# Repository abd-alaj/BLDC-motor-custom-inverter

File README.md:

Hello, 

this is the start of our casptone project. 

You will see the following structure (with changes if i have forgotten to update this section):  

```
.
├── data/                    - parameters, csv files, oscilloscope data
├── docs/                    - documentation of our project
├── hardware/                - KiCad Project files, scheamtic, footprints, etc.
│   ├── schematics/             - schematic files
│   ├── layout/                 - PCB layout files
│   ├── libraries/              - custom footprints/symbols
│   └── manufacturing/          - gerbers, BOM, etc.
├── models/                 - main simulink directory
│   └── components/              - smaller components for the model
├── scripts/                 - utility matlab scripts
├── src/                     - C code
└── work/                    - MATLAB throws autogenerated files in here 
```

# How To Use This Code
1. git clone this repo: 
```
git clone https://github.com/abd-alaj/BLDC-motor-custom-inverter.git
```
2. open the `BLDC_motor_custom_inverter.m.prj` file in matlab prior to starting any work.

That's it. This project is in a rather primitive state so this readme file is an active WIP.

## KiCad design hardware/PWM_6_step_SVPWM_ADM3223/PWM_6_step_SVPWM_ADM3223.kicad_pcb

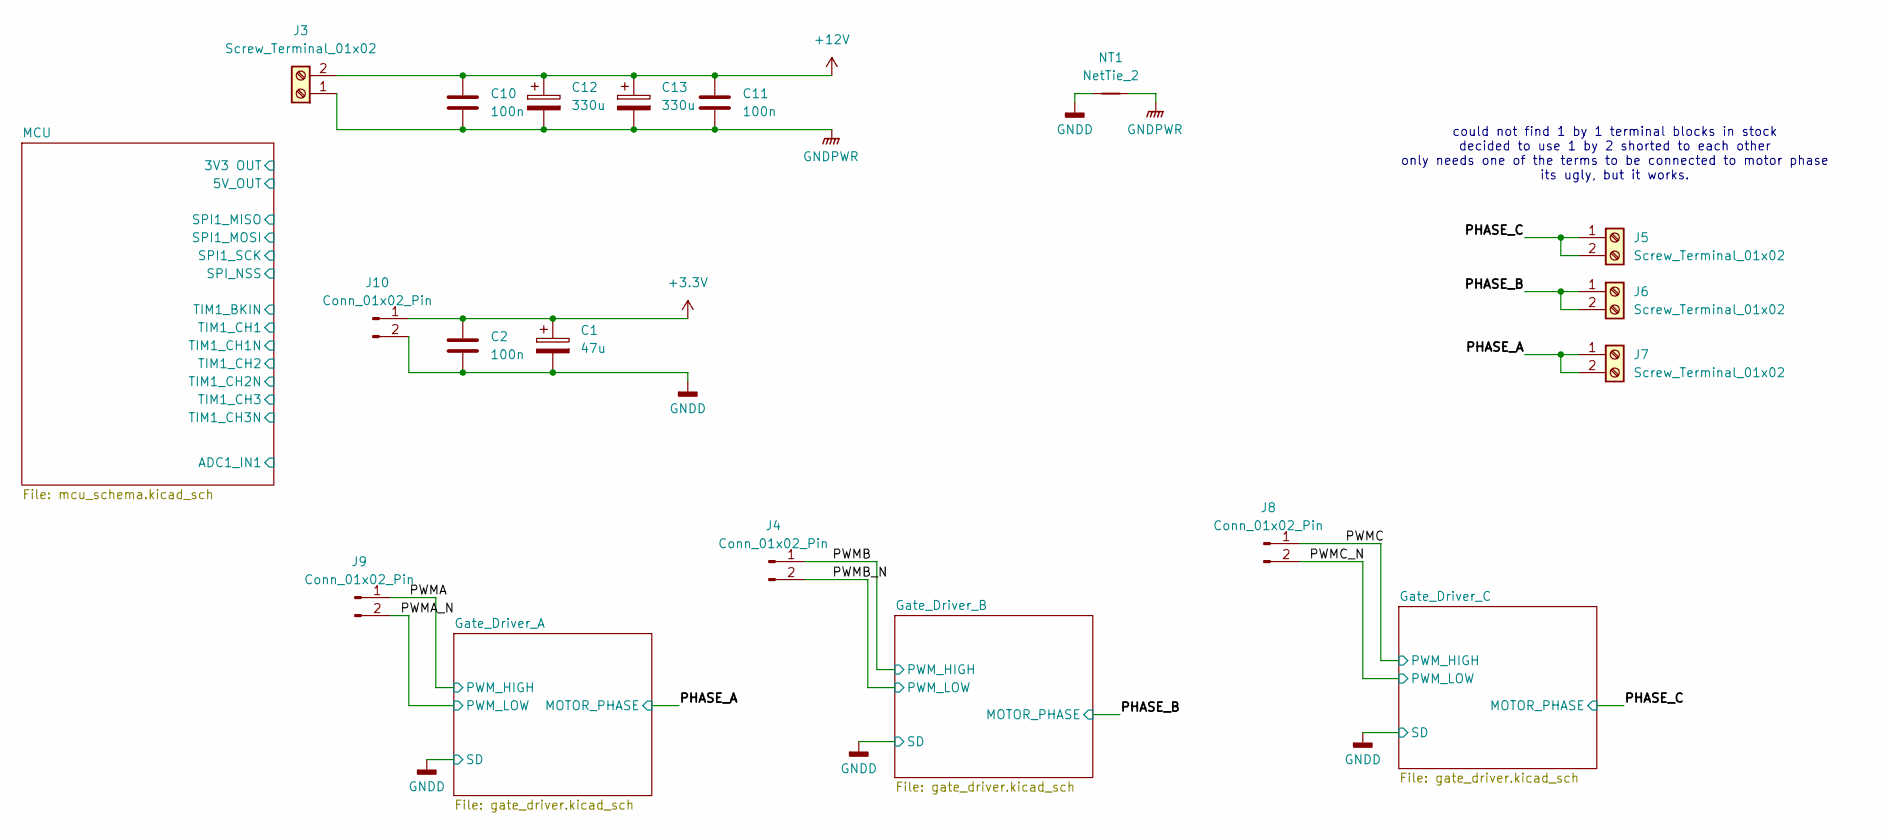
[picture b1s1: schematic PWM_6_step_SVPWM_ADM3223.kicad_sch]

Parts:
C1: 47u; CP_Radial_D8.0mm_P3.50mm
C2, C10, C11: 100n; C_1206_3216Metric
C12, C13: 330u; PCAP_12_5x20-THRU-ELECT_NCA
J3, J5, J6, J7: Screw_Terminal_01x02; TerminalBlock_TE_282834-2_1x02_P2.54mm_Horizontal
J4, J8, J9, J10: Conn_01x02_Pin; PinHeader_1x02_P2.54mm_Vertical
NT1: NetTie_2; NetTie-2_SMD_Pad2.0mm

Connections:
+3.3V: C1.1, C2.1, J10.1; also elsewhere on the board
+12V: C10.1, C11.1, C12.1, C13.1, J3.2; also elsewhere on the board
/PHASE_A: J7.1, J7.2; also elsewhere on the board
/PHASE_B: J6.1, J6.2; also elsewhere on the board
/PHASE_C: J5.1, J5.2; also elsewhere on the board
/PWMA: J9.1; also elsewhere on the board
/PWMA_N: J9.2; also elsewhere on the board
/PWMB: J4.1; also elsewhere on the board
/PWMB_N: J4.2; also elsewhere on the board
/PWMC: J8.1; also elsewhere on the board
/PWMC_N: J8.2; also elsewhere on the board
GNDD: C1.2, C2.2, J10.2, NT1.1; also elsewhere on the board
GNDPWR: C10.2, C11.2, C12.2, C13.2, J3.1, NT1.2; also elsewhere on the board

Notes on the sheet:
could not find 1 by 1 terminal blocks in stock decided to use 1 by 2 shorted to each other only needs one of the terms to be connected to motor phase its ugly, but it works.

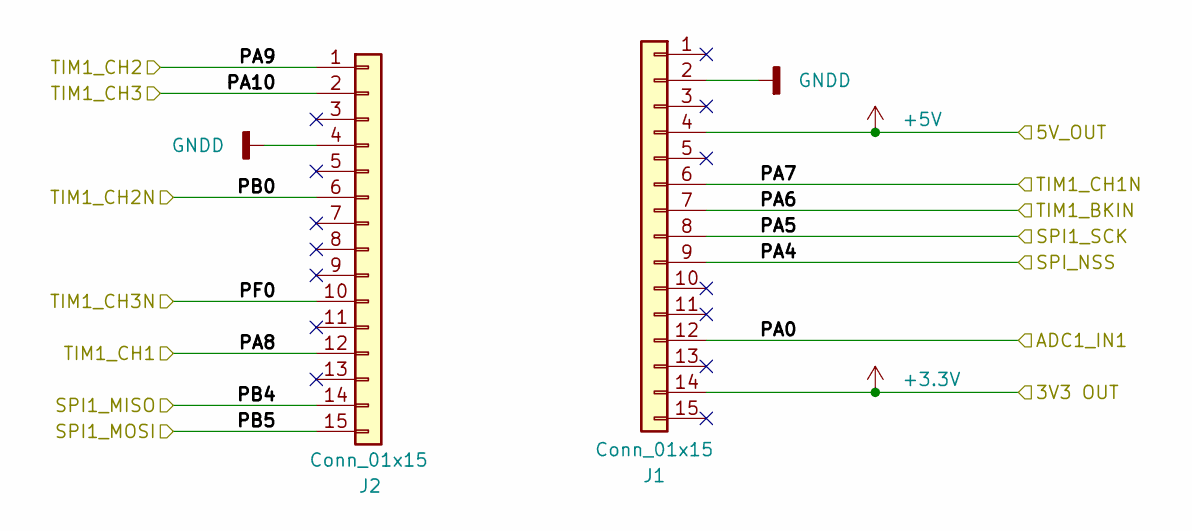
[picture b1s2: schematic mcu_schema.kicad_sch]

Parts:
J1, J2: Conn_01x15; PinSocket_1x15_P2.54mm_Vertical

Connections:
unnamed: J1.2, J2.4

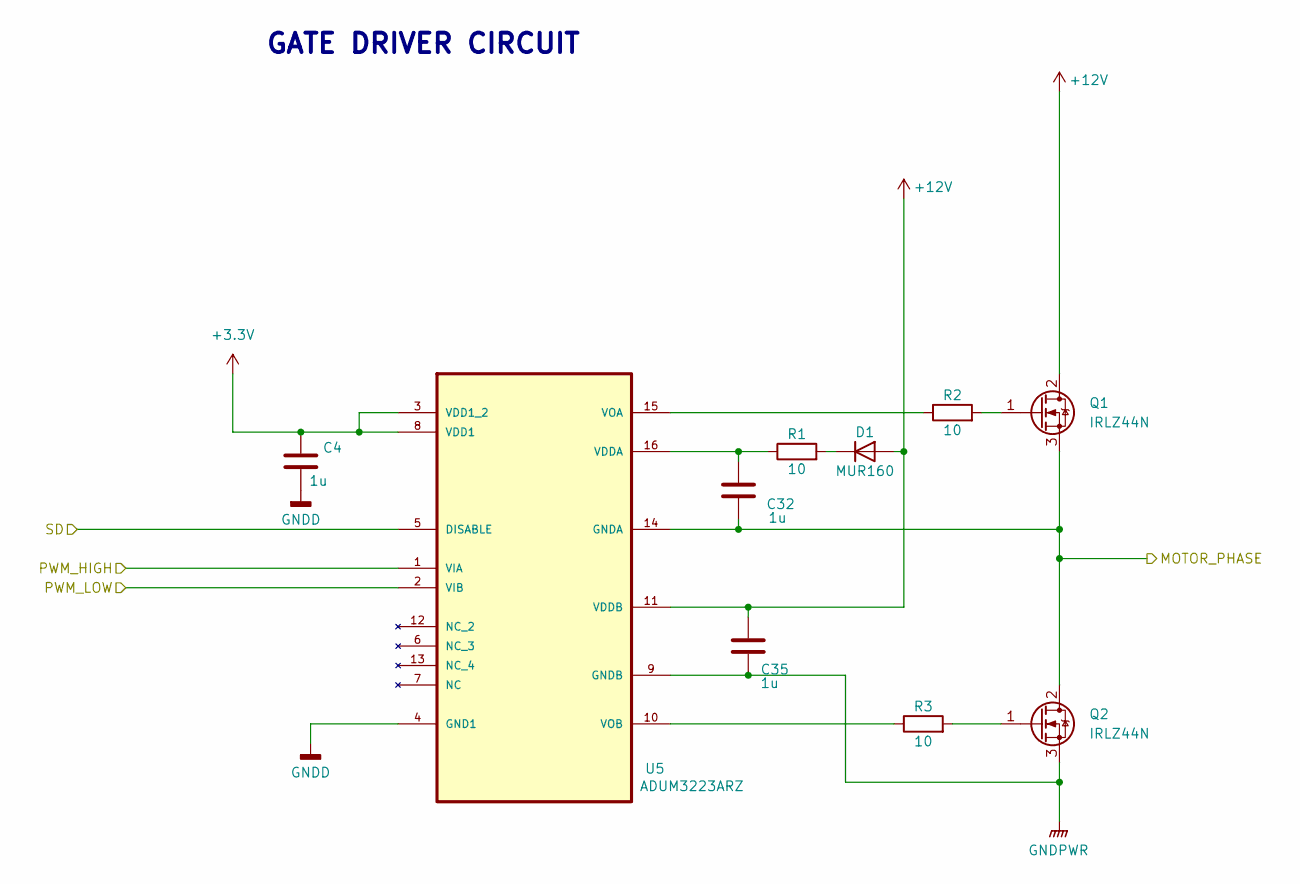
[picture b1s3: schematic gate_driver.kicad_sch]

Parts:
C4, C32, C35: 1u; C_0603_1608Metric
D1: MUR160; D_DO-41_SOD81_P7.62mm_Horizontal
Q1, Q2: IRLZ44N; TO-220-3_Vertical
R1, R2, R3: 10; R_1206_3216Metric
U5: ADUM3223ARZ; SOIC127P600X175-16N; MPN ADUM3223ARZ

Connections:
+3.3V: C4.1, U5.3 (VDD1_2), U5.8 (VDD1); also elsewhere on the board
+12V: C35.1, D1.2 (A), Q1.2 (D), U5.11 (VDDB); also elsewhere on the board
/PHASE_A: C32.2, Q1.3 (S), Q2.2 (D), U5.14 (GNDA); also elsewhere on the board
/PWMA: U5.1 (VIA); also elsewhere on the board
/PWMA_N: U5.2 (VIB); also elsewhere on the board
GNDD: C4.2, U5.4 (GND1), U5.5 (DISABLE); also elsewhere on the board
GNDPWR: C35.2, Q2.3 (S), U5.9 (GNDB); also elsewhere on the board
unnamed: D1.1 (K), R1.2
unnamed: Q1.1 (G), R2.2
unnamed: Q2.1 (G), R3.2
unnamed: C32.1, R1.1, U5.16 (VDDA)
unnamed: R2.1, U5.15 (VOA)
unnamed: R3.1, U5.10 (VOB)

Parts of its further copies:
C5, C9, C33, C34, C36, C37: 1u; C_0603_1608Metric
D2, D3: MUR160; D_DO-41_SOD81_P7.62mm_Horizontal
Q3, Q4, Q5, Q6: IRLZ44N; TO-220-3_Vertical
R4, R5, R6, R7, R8, R9: 10; R_1206_3216Metric
U6, U7: ADUM3223ARZ; SOIC127P600X175-16N; MPN ADUM3223ARZ

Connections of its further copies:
+3.3V: C5.1, C9.1, U6.3 (VDD1_2), U6.8 (VDD1), U7.3 (VDD1_2), U7.8 (VDD1); also elsewhere on the board
+12V: C36.1, C37.1, D2.2 (A), D3.2 (A), Q3.2 (D), Q5.2 (D), U6.11 (VDDB), U7.11 (VDDB); also elsewhere on the board
/PHASE_B: C33.2, Q3.3 (S), Q4.2 (D), U6.14 (GNDA); also elsewhere on the board
/PHASE_C: C34.2, Q5.3 (S), Q6.2 (D), U7.14 (GNDA); also elsewhere on the board
/PWMB: U6.1 (VIA); also elsewhere on the board
/PWMB_N: U6.2 (VIB); also elsewhere on the board
/PWMC: U7.1 (VIA); also elsewhere on the board
/PWMC_N: U7.2 (VIB); also elsewhere on the board
GNDD: C5.2, C9.2, U6.4 (GND1), U6.5 (DISABLE), U7.4 (GND1), U7.5 (DISABLE); also elsewhere on the board
GNDPWR: C36.2, C37.2, Q4.3 (S), Q6.3 (S), U6.9 (GNDB), U7.9 (GNDB); also elsewhere on the board
unnamed: D2.1 (K), R4.2
unnamed: D3.1 (K), R7.2
unnamed: Q3.1 (G), R6.2
unnamed: Q4.1 (G), R5.2
unnamed: Q5.1 (G), R9.2
unnamed: Q6.1 (G), R8.2
unnamed: C33.1, R4.1, U6.16 (VDDA)
unnamed: R6.1, U6.15 (VOA)
unnamed: R5.1, U6.10 (VOB)
unnamed: C34.1, R7.1, U7.16 (VDDA)
unnamed: R9.1, U7.15 (VOA)
unnamed: R8.1, U7.10 (VOB)

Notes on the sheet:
GATE DRIVER CIRCUIT

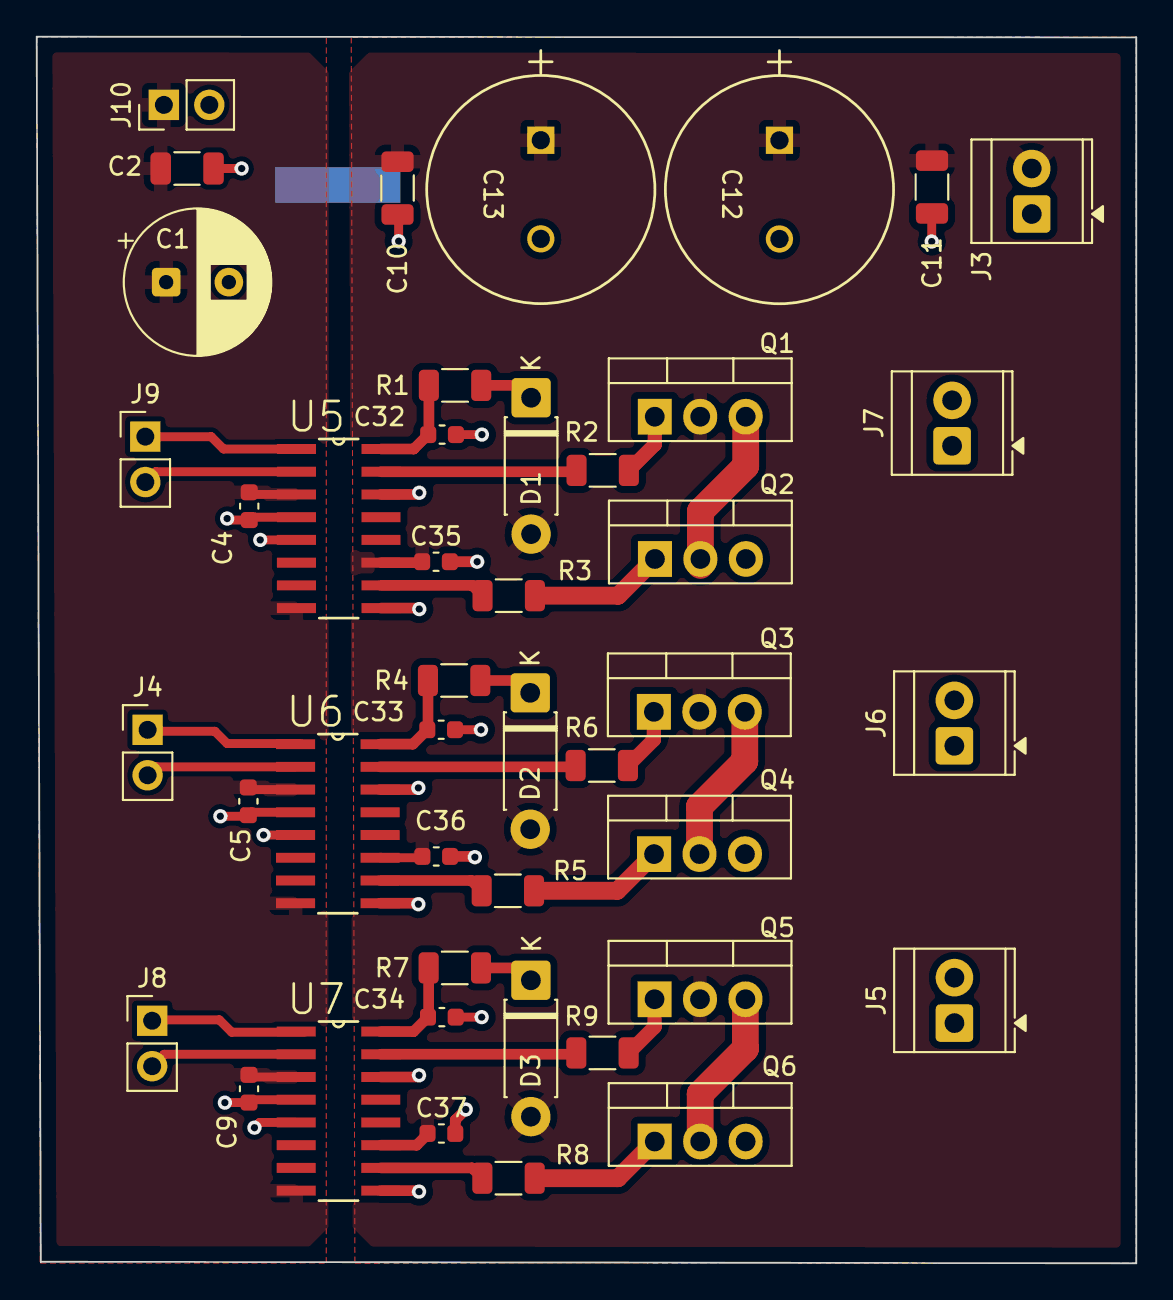
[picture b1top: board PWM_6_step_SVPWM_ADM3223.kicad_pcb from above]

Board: 2 copper layers, 61.4 x 68.5 mm, 45 parts (1 on the bottom side), 31 nets.

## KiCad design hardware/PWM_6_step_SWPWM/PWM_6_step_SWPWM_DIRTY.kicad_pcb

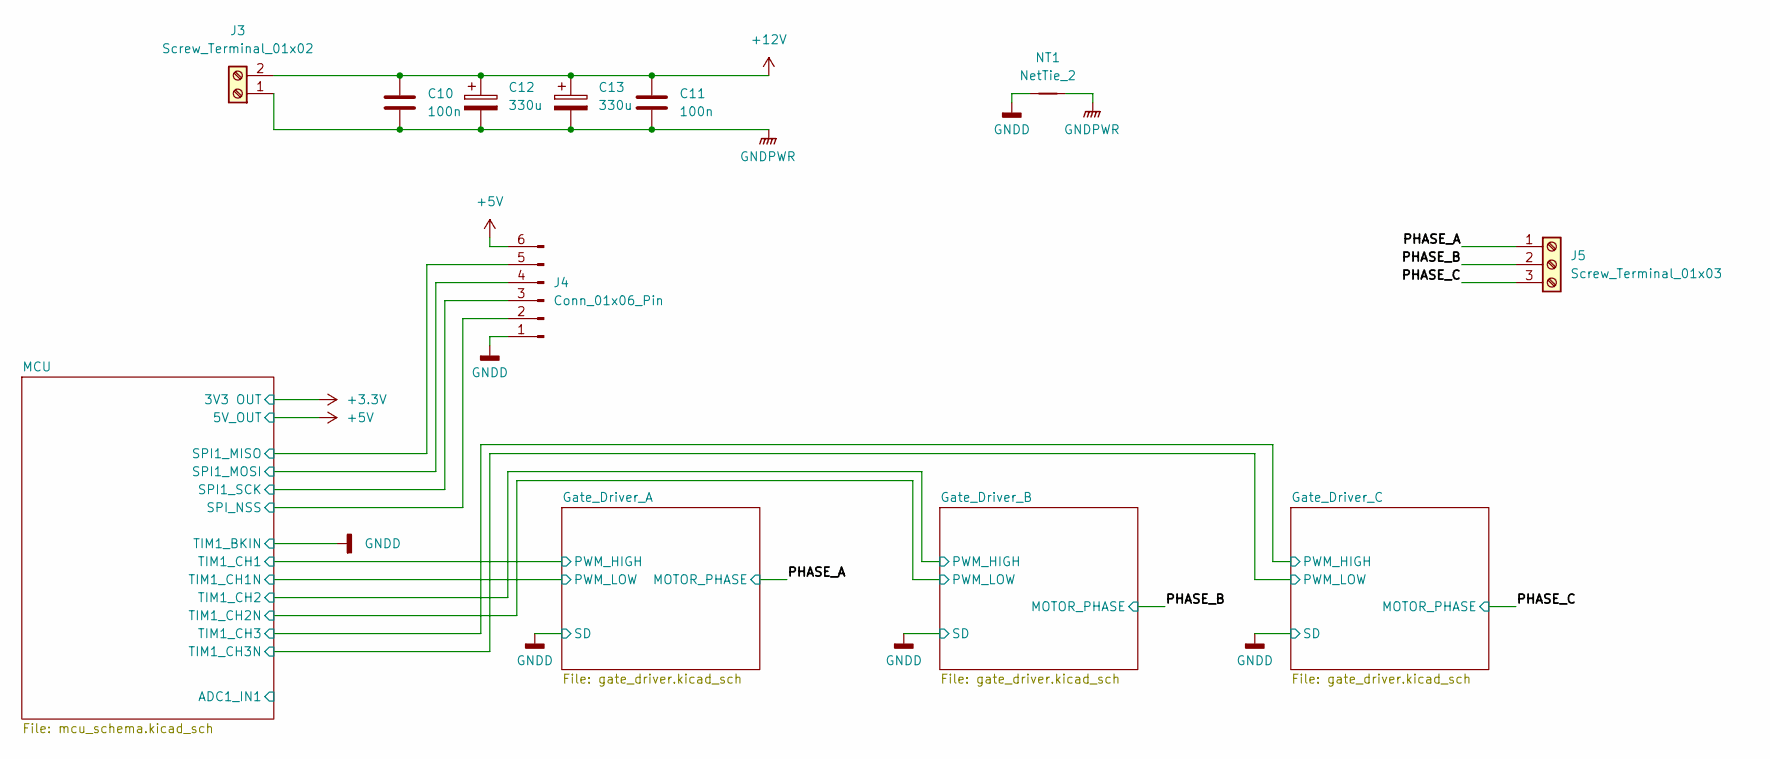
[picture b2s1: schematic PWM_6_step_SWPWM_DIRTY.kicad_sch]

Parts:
C10, C11: 100n; C_1206_3216Metric
C12, C13: 330u; PCAP_12_5x20-THRU-ELECT_NCA
J3: Screw_Terminal_01x02; TerminalBlock_TE_282834-2_1x02_P2.54mm_Horizontal
J4: Conn_01x06_Pin; PinHeader_1x06_P2.54mm_Vertical
J5: Screw_Terminal_01x03; TerminalBlock_TE_282834-3_1x03_P2.54mm_Horizontal
NT1: NetTie_2; NetTie-2_SMD_Pad2.0mm

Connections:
+5V: J4.6; also elsewhere on the board
+12V: C10.1, C11.1, C12.1, C13.1, J3.2; also elsewhere on the board
/MCU/PA4: J4.2; also elsewhere on the board
/MCU/PA5: J4.3; also elsewhere on the board
/MCU/PB4: J4.5; also elsewhere on the board
/MCU/PB5: J4.4; also elsewhere on the board
/PHASE_A: J5.1; also elsewhere on the board
/PHASE_B: J5.2; also elsewhere on the board
/PHASE_C: J5.3; also elsewhere on the board
GNDD: J4.1, NT1.1; also elsewhere on the board
GNDPWR: C10.2, C11.2, C12.2, C13.2, J3.1, NT1.2; also elsewhere on the board

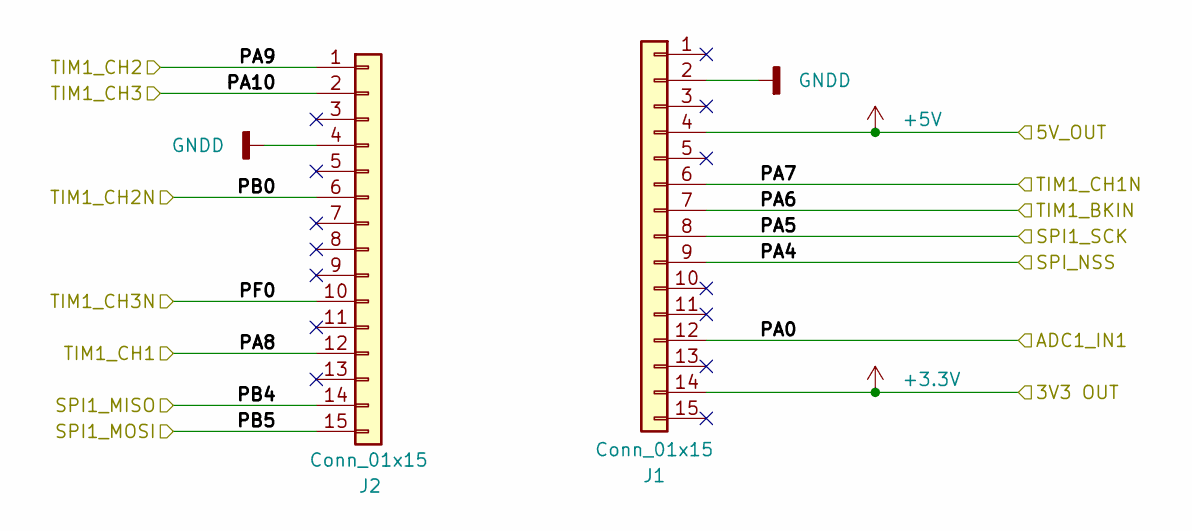
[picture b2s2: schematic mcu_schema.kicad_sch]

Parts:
J1, J2: Conn_01x15; PinSocket_1x15_P2.54mm_Vertical

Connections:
+3.3V: J1.14; also elsewhere on the board
+5V: J1.4; also elsewhere on the board
/MCU/PA0: J1.12
/MCU/PA4: J1.9; also elsewhere on the board
/MCU/PA5: J1.8; also elsewhere on the board
/MCU/PA7: J1.6; also elsewhere on the board
/MCU/PA8: J2.12; also elsewhere on the board
/MCU/PA9: J2.1; also elsewhere on the board
/MCU/PA10: J2.2; also elsewhere on the board
/MCU/PB0: J2.6; also elsewhere on the board
/MCU/PB4: J2.14; also elsewhere on the board
/MCU/PB5: J2.15; also elsewhere on the board
/MCU/PF0: J2.10; also elsewhere on the board
GNDD: J1.2, J1.7, J2.4; also elsewhere on the board

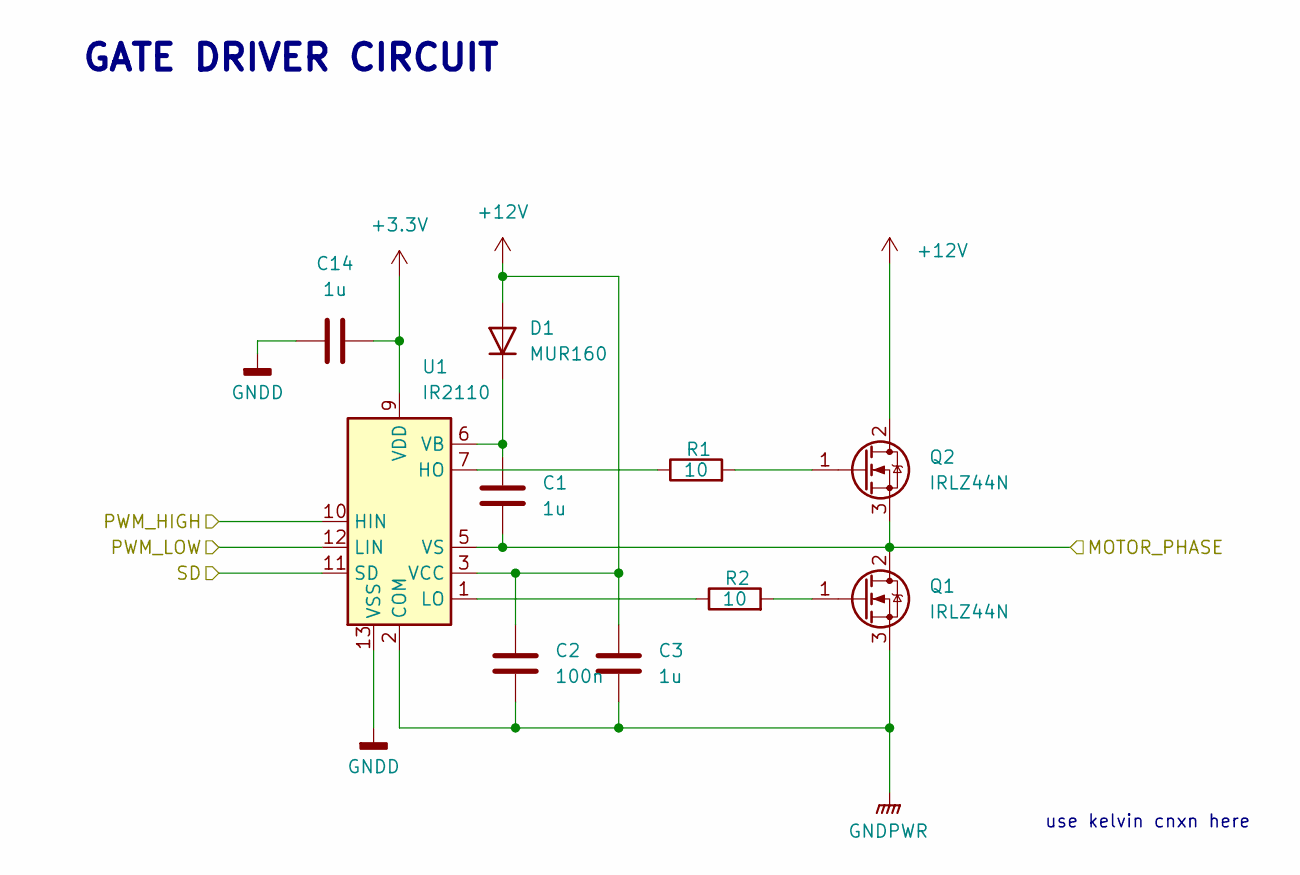
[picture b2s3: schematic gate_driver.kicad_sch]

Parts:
C1, C3: 1u; C_1206_3216Metric
C2: 100n; C_1206_3216Metric
C14: 1u; C_0603_1608Metric
D1: MUR160; D_DO-41_SOD81_P10.16mm_Horizontal
Q1, Q2: IRLZ44N; TO-220-3_Vertical
R1, R2: 10; R_1206_3216Metric
U1: IR2110; DIP-14_W7.62mm

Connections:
+3.3V: C14.2, U1.9 (VDD); also elsewhere on the board
+12V: C2.1, C3.1, D1.2 (A), Q2.2 (D), U1.3 (VCC); also elsewhere on the board
/MCU/PA7: U1.12 (LIN); also elsewhere on the board
/MCU/PA8: U1.10 (HIN); also elsewhere on the board
/PHASE_A: C1.2, Q1.2 (D), Q2.3 (S), U1.5 (VS); also elsewhere on the board
GNDD: C14.1, U1.11 (SD), U1.13 (VSS); also elsewhere on the board
GNDPWR: C2.2, C3.2, Q1.3 (S), U1.2 (COM); also elsewhere on the board
unnamed: C1.1, D1.1 (K), U1.6 (VB)
unnamed: Q1.1 (G), R2.2
unnamed: Q2.1 (G), R1.2
unnamed: R1.1, U1.7 (HO)
unnamed: R2.1, U1.1 (LO)

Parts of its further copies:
C4, C6, C7, C9: 1u; C_1206_3216Metric
C5, C8: 100n; C_1206_3216Metric
C15, C16: 1u; C_0603_1608Metric
D2, D3: MUR160; D_DO-41_SOD81_P10.16mm_Horizontal
Q3, Q4, Q5, Q6: IRLZ44N; TO-220-3_Vertical
R3, R4, R5, R6: 10; R_1206_3216Metric
U2, U3: IR2110; DIP-14_W7.62mm

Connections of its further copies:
+3.3V: C15.2, C16.2, U2.9 (VDD), U3.9 (VDD); also elsewhere on the board
+12V: C5.1, C6.1, C8.1, C9.1, D2.2 (A), D3.2 (A), Q3.2 (D), Q5.2 (D), U2.3 (VCC), U3.3 (VCC); also elsewhere on the board
/MCU/PA9: U2.10 (HIN); also elsewhere on the board
/MCU/PA10: U3.10 (HIN); also elsewhere on the board
/MCU/PB0: U2.12 (LIN); also elsewhere on the board
/MCU/PF0: U3.12 (LIN); also elsewhere on the board
/PHASE_B: C4.2, Q3.3 (S), Q4.2 (D), U2.5 (VS); also elsewhere on the board
/PHASE_C: C7.2, Q5.3 (S), Q6.2 (D), U3.5 (VS); also elsewhere on the board
GNDD: C15.1, C16.1, U2.11 (SD), U2.13 (VSS), U3.11 (SD), U3.13 (VSS); also elsewhere on the board
GNDPWR: C5.2, C6.2, C8.2, C9.2, Q4.3 (S), Q6.3 (S), U2.2 (COM), U3.2 (COM); also elsewhere on the board
unnamed: C4.1, D2.1 (K), U2.6 (VB)
unnamed: C7.1, D3.1 (K), U3.6 (VB)
unnamed: Q3.1 (G), R3.2
unnamed: Q4.1 (G), R4.2
unnamed: Q5.1 (G), R5.2
unnamed: Q6.1 (G), R6.2
unnamed: R3.1, U2.7 (HO)
unnamed: R4.1, U2.1 (LO)
unnamed: R5.1, U3.7 (HO)
unnamed: R6.1, U3.1 (LO)

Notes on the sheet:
GATE DRIVER CIRCUIT
use kelvin cnxn here

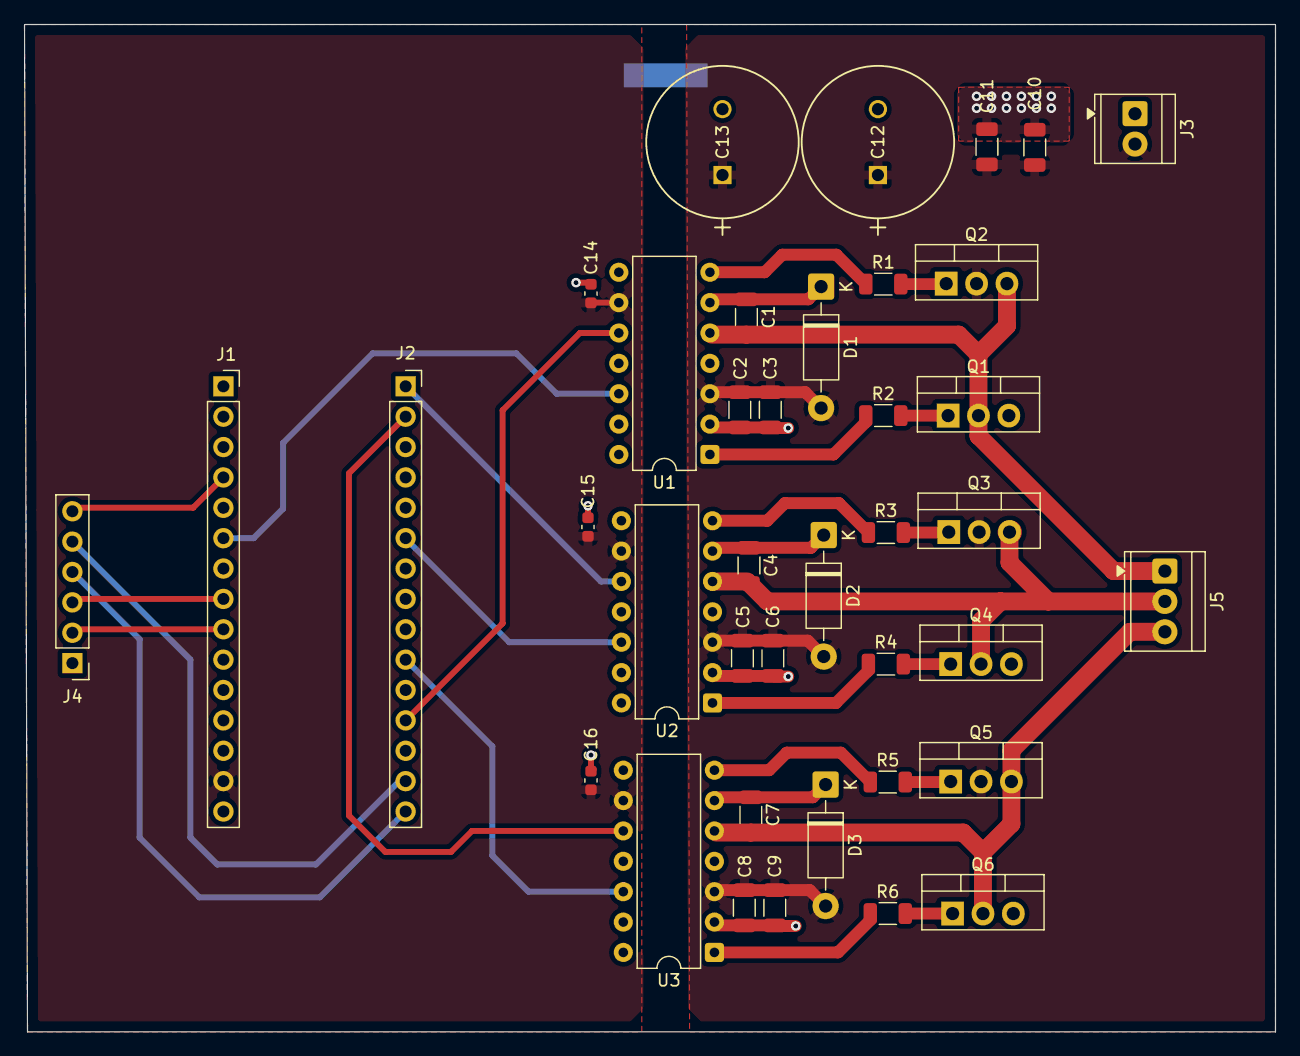
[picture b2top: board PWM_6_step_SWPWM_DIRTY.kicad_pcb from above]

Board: 2 copper layers, 104.6 x 84.2 mm, 40 parts (1 on the bottom side), 33 nets.

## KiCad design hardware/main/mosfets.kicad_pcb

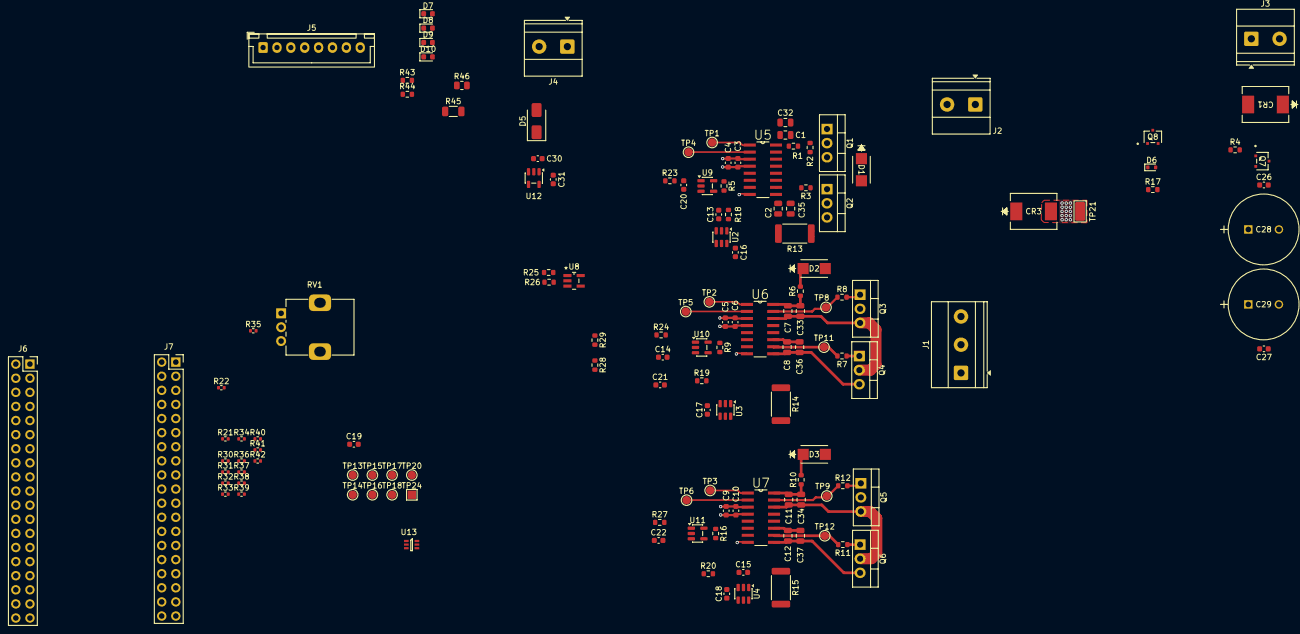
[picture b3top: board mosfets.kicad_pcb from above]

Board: 4 copper layers, 139 parts (1 on the bottom side), 67 nets.

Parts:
C1, C2, C7, C8, C11, C12: 100n; C_0805_2012Metric
C3, C6, C10, C13, C14, C15, C16, C17, C18, C19, C20, C21, C22, C26, C27: 100n; C_0603_1608Metric
C4, C5, C9: 10u; C_0603_1608Metric
C28, C29: 330u; PCAP_12_5x20-THRU-ELECT_NCA
C30, C31: 1u; C_0603_1608Metric
C32, C33, C34, C35, C36, C37: 10u; C_0805_2012Metric
CR1, CR3: SMCJ26; SMCJSeries_LTF
D1, D2, D3: MURA160T3G
D4, D6: MM5Z10VT1G; D_SOD-523
D5: SS14; D_SMA
D7, D8, D9, D10: LED; LED_0603_1608Metric
J1: Screw_Terminal_01x03; TerminalBlock_Phoenix_MKDS-1,5-3-5.08_1x03_P5.08mm_Horizont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
J2, J3, J4: Screw_Terminal_01x02; TerminalBlock_Phoenix_MKDS-1,5-2-5.08_1x02_P5.08mm_Horizont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
J5: Conn_01x08_Pin; JST_XH_B8B-XH-A_1x08_P2.50mm_Vertical
J6, J7: Conn_02x19_Odd_Even; PinSocket_2x19_P2.54mm_Vertical
Q1, Q2, Q3, Q4, Q5, Q6: IRLZ44N; TO-220-3_Vertical
Q7, Q8: SSM3J351R
R1, R2, R3, R6, R7, R8, R10, R11, R12: 10; R_0603_1608Metric
R4, R17: 47k; R_0603_1608Metric
R5, R9, R16: 4.7k; R_0603_1608Metric
R13, R14, R15: 10m; R_2512_6332Metric
R18, R19, R20, R28: 3.3k; R_0603_1608Metric
R21, R22, R30, R31, R32, R33, R34, R35, R36, R37, R38, R39, R40, R41, R42: 0; R_0402_1005Metric
R23, R24, R27, R43: 680; R_0603_1608Metric
R25, R26: 10k; R_0603_1608Metric
R29: 33k; R_0603_1608Metric
R44: 100; R_0603_1608Metric
R45: 6.98k; R_1206_3216Metric
R46: 3k; R_0805_2012Metric
RV1: 10k; Potentiometer_Alps_RK09K_Single_Vertical
TP1, TP2, TP3, TP4, TP5, TP6, TP8, TP9, TP11, TP12, TP13, TP14, TP15, TP16, TP17, TP18, TP20: TestPoint; TestPoint_Pad_D1.5mm
TP21: Keystone 5015; TestPoint_Keystone_5015_Micro_Mini
TP24: TestPoint; TestPoint_Pad_1.5x1.5mm
U2, U3, U4: INA181; SOT-23-6
U5, U6, U7: ADUM3223ARZ; SOIC127P600X175-16N
U8: LMV321; LMV321DBV5
U9, U10, U11: TL331; SOT-23-5
U12: AP2112K-3.3; SOT-23-5
U13: 74LVC1G332; 74LVC1G332_DCK0006A_N

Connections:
+3.3V: C3.1, C4.1, C5.1, C6.1, C9.1, C10.1, C16.1, C17.1, C18.1, C19.1, C31.1, R5.1, R9.1, R16.1, R25.2, R29.1, R44.1, RV1.3, U2.6 (V+), U3.6 (V+), U4.6 (V+), U5.3 (VDD1_2), U5.8 (VDD1), U6.3 (VDD1_2), U6.8 (VDD1), U7.3 (VDD1_2), U7.8 (VDD1), U8.5 (V+), U9.5 (V+), U10.5 (V+), U11.5 (V+), U12.5 (VOUT), U13.5 (VCC)
+5V: D5.2 (A), J4.2
+12V: C2.1, C8.1, C12.1, C35.1, C36.1, C37.1, D1.2 (A), D2.2 (A), D3.2 (A), D6.1 (K), Q8.3 (S), R46.1, U5.11 (VDDB), U6.11 (VDDB), U7.11 (VDDB)
+24V: C26.1, C27.1, C28.1, C29.1, D4.1 (K), Q1.2 (D), Q3.2 (D), Q5.2 (D), Q7.3 (S), R45.1
/ADC_SENS_A: C13.1, J7.28, R18.2, R36.1, R36.2, TP13.1 (1_1)
/ADC_SENS_B: C14.1, J7.36, R19.2, R41.1, R41.2, TP14.1 (1_1)
/ADC_SENS_C: C15.1, J7.38, R20.2, R42.1, R42.2, TP15.1 (1_1)
/BRK_IN: J6.13, R34.1, R34.2, U13.4
/MCU/ADC_SPEED_CTRL: J7.37, R35.1
/MCU/PWMN_A: J6.15, R21.1, R21.2, TP4.1 (1_1), U5.2 (VIB)
/MCU/PWMN_B: J7.34, R30.1, R30.2, TP5.1 (1_1), U6.2 (VIB)
/MCU/PWMN_C: J6.24, R32.1, R32.2, TP6.1 (1_1), U7.2 (VIB)
/MCU/PWM_A: J6.23, R22.1, R22.2, TP1.1 (1_1), U5.1 (VIA)
/MCU/PWM_B: J6.21, R31.1, R31.2, TP2.1 (1_1), U6.1 (VIA)
/MCU/PWM_C: J6.33, R33.1, R33.2, TP3.1 (1_1), U7.1 (VIA)
/MCU/SPI_CS: J5.7, J6.17, R40.1, R40.2
/MCU/SPI_MISO: J5.4, J6.27, R38.1, R38.2
/MCU/SPI_MOSI: J5.5, J6.29, R39.1, R39.2
/MCU/SPI_SCK: J5.6, J6.11, R37.1, R37.2
/OCP_Current_Sens/VSHUNT_A_P: C2.2, C35.2, Q2.3 (S), R13.1, U2.3 (+), U5.9 (GNDB), U9.3 (+)
/OCP_Current_Sens/VSHUNT_B_P: C8.2, C36.2, Q4.3 (S), R14.1, U3.3 (+), U6.9 (GNDB), U10.3 (+)
/OCP_Current_Sens/VSHUNT_C_P: C12.2, C37.2, Q6.3 (S), R15.1, U4.3 (+), U7.9 (GNDB), U11.3 (+)
/OCP_Current_Sens/V_BIAS: TP17.1 (1_1), U2.5 (REF), U3.5 (REF), U4.5 (REF), U8.3 (-), U8.4
/OCP_Current_Sens/V_REF: R23.1, R24.1, R27.1, R28.2, R29.2, TP16.1 (1_1)
/PHASE_A: C1.2, C32.2, J1.3, Q1.3 (S), Q2.2 (D), U5.14 (GNDA)
/PHASE_B: C7.2, C33.2, J1.2, Q3.3 (S), Q4.2 (D), U6.14 (GNDA)
/PHASE_C: C11.2, C34.2, J1.1, Q5.3 (S), Q6.2 (D), U7.14 (GNDA)
/Power Management/5V_STATUS_LED: C30.1, D5.1 (K), R43.1, U12.1 (VIN), U12.3 (EN)
/Power Management/12V_EXT: CR3.1, J2.2, Q8.1 (D)
/Power Management/24V_EXT: CR1.1, J3.2, Q7.1 (D)
/SD_A: R5.2, TP18.1 (1_1), U5.5 (DISABLE), U9.4, U13.6
/SD_B: R9.2, TP24.1 (1_1), U6.5 (DISABLE), U10.4, U13.1
/SD_C: R16.2, TP20.1 (1_1), U7.5 (DISABLE), U11.4, U13.3
GNDA: C3.2, C4.2, C5.2, C6.2, C9.2, C10.2, C13.2, C14.2, C15.2, C16.2, C17.2, C18.2, C19.2, C20.2, C21.2, C22.2, C30.2, C31.2, D7.1 (K), D8.1 (K), J4.1, J5.1, J5.2, J5.8, J6.9, J6.20, J6.32, J7.8, J7.19, J7.20, J7.22, R26.2, R28.1, RV1.1, U2.2 (GND), U3.2 (GND), U4.2 (GND), U5.4 (GND1), U6.4 (GND1), U7.4 (GND1), U8.2 (V-), U9.2 (V-), U10.2 (V-), U11.2 (V-), U12.2 (GND), U13.2 (GND)
GNDPWR: C26.2, C27.2, C28.2, C29.2, CR1.2, CR3.2, D9.1 (K), D10.1 (K), J2.1, J3.1, R4.2, R13.2, R14.2, R15.2, R17.2, TP21.1 (1_1), U2.4 (-), U3.4 (-), U4.4 (-)
unnamed: D1.1 (K), R1.2
unnamed: D2.1 (K), R6.2
unnamed: D3.1 (K), R10.2
unnamed: D4.2 (A), Q7.2 (G), R4.1
unnamed: D6.2 (A), Q8.2 (G), R17.1
unnamed: D7.2 (A), R43.2
unnamed: D8.2 (A), R44.2
unnamed: D9.2 (A), R45.2
unnamed: D10.2 (A), R46.2
unnamed: Q1.1 (G), R2.2
unnamed: Q2.1 (G), R3.2
unnamed: Q3.1 (G), R8.2
unnamed: Q4.1 (G), R7.2
unnamed: Q5.1 (G), R12.2
unnamed: Q6.1 (G), R11.2
unnamed: R18.1, U2.1
unnamed: R19.1, U3.1
unnamed: R20.1, U4.1
unnamed: R35.2, RV1.2
unnamed: C1.1, C32.1, R1.1, U5.16 (VDDA)
unnamed: R2.1, U5.15 (VOA)
unnamed: R3.1, U5.10 (VOB)
unnamed: C7.1, C33.1, R6.1, U6.16 (VDDA)
unnamed: R8.1, TP8.1 (1_1), U6.15 (VOA)
unnamed: R7.1, TP11.1 (1_1), U6.10 (VOB)
unnamed: C11.1, C34.1, R10.1, U7.16 (VDDA)
unnamed: R12.1, TP9.1 (1_1), U7.15 (VOA)
unnamed: R11.1, TP12.1 (1_1), U7.10 (VOB)
unnamed: R25.1, R26.1, U8.1 (+)
unnamed: C20.1, R23.2, U9.1 (-)
unnamed: C21.1, R24.2, U10.1 (-)
unnamed: C22.1, R27.2, U11.1 (-)

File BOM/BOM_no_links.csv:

"Reference","Qty","Value","DNP","Exclude from BOM","Exclude from Board","Footprint","Datasheet"
"C1,C2,C3,C6,C7,C8,C10,C11,C12,C13,C14,C15,C16,C17,C18,C19,C20,C21,C22,C26,C27","21","100n","","","","Capacitor_SMD:C_0603_1608Metric",""
"C4,C5,C9","3","4.7u","","","","Capacitor_SMD:C_0603_1608Metric",""
"C28,C29","2","330u","","","","footprint:PCAP_12_5x20-THRU-ELECT_NCA",""
"C30,C31","2","1u","","","","Capacitor_SMD:C_0603_1608Metric",""
"C32,C33,C34,C35,C36,C37","6","10u","","","","Capacitor_SMD:C_0805_2012Metric",""
"CR1,CR3","2","SMCJ26","","","","footprint:SMCJSeries_LTF","SMCJ26"
"D1,D2,D3","3","MURA160T3G","","","","footprint:MURA160T3G",""
"D4,D6","2","MM5Z10VT1G","","","","Diode_SMD:D_SOD-523","https://diotec.com/tl_files/diotec/files/pdf/datasheets/mm5z2v4.pdf"
"D5","1","SS14","","","","Diode_SMD:D_SMA","https://www.vishay.com/docs/88746/ss12.pdf"
"D7,D8,D9,D10","4","LED","","","","LED_SMD:LED_0603_1608Metric",""
"J1","1","Screw_Terminal_01x03","","","","TerminalBlock_Phoenix:TerminalBlock_Phoenix_MKDS-1,5-3-5.08_1x03_P5.08mm_Horizontal",""
"J2,J3,J4","3","Screw_Terminal_01x02","","","","TerminalBlock_Phoenix:TerminalBlock_Phoenix_MKDS-1,5-2-5.08_1x02_P5.08mm_Horizontal",""
"J5","1","Conn_01x08_Pin","","","","Connector_JST:JST_XH_B8B-XH-A_1x08_P2.50mm_Vertical",""
"Q1,Q2,Q3,Q4,Q5,Q6","6","IRLZ44N","","","","Package_TO_SOT_THT:TO-220-3_Vertical","http://www.irf.com/product-info/datasheets/data/irlz44n.pdf"
"Q7,Q9","2","DMP6050SSD","","","","Package_SO:SOIC-8_3.9x4.9mm_P1.27mm","https://www.diodes.com/assets/Datasheets/DMP6050SSD.pdf"
"R1,R2,R3,R6,R7,R8,R10,R11,R12","9","10","","","","Resistor_SMD:R_0603_1608Metric",""
"R4,R17","2","47k","","","","Resistor_SMD:R_0603_1608Metric",""
"R5,R9,R16","3","4.7k","","","","Resistor_SMD:R_0603_1608Metric",""
"R13,R14,R15","3","10m","","","","Resistor_SMD:R_2512_6332Metric",""
"R18,R19,R20,R28","4","3.3k","","","","Resistor_SMD:R_0603_1608Metric",""
"R21,R22,R30,R31,R32,R33,R34,R35,R36,R37,R38,R39,R40,R41,R42","15","0","","","","Resistor_SMD:R_0402_1005Metric",""
"R23,R24,R27","3","680","","","","Resistor_SMD:R_0603_1608Metric",""
"R25,R26","2","10k","","","","Resistor_SMD:R_0603_1608Metric",""
"R29","1","33k","","","","Resistor_SMD:R_0603_1608Metric",""
"R43","1","680","","","","Resistor_SMD:R_0603_1608Metric_Pad0.98x0.95mm_HandSolder",""
"R44","1","100","","","","Resistor_SMD:R_0603_1608Metric_Pad0.98x0.95mm_HandSolder",""
"R45","1","6.98k","","","","Resistor_SMD:R_1206_3216Metric_Pad1.30x1.75mm_HandSolder",""
"R46","1","3k","","","","Resistor_SMD:R_0805_2012Metric_Pad1.20x1.40mm_HandSolder",""
"RV1","1","10k","","","","Potentiometer_THT:Potentiometer_Alps_RK09K_Single_Vertical",""
"TP1,TP2,TP3,TP4,TP5,TP6,TP7,TP8,TP9,TP10,TP11,TP12,TP13,TP14,TP15,TP16,TP17,TP18,TP20,TP24","20","TestPoint","","","","TestPoint:TestPoint_Pad_1.5x1.5mm",""
"TP21,TP22,TP23","3","Keystone 5015","","","","TestPoint:TestPoint_Keystone_5015_Micro_Mini",""
"U1","1","NUCLEO64-F411RE","","","","Module:ST_Morpho_Connector_144_STLink","http://www.st.com/st-web-ui/static/active/en/resource/techni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"
"U2,U3,U4","3","INA181","","","","Package_TO_SOT_SMD:SOT-23-6","http://www.ti.com/lit/ds/symlink/ina181.pdf"
"U5,U6,U7","3","ADUM3223ARZ","","","","footprint:SOIC127P600X175-16N",""
"U8","1","LMV321","","","","footprint:LMV321DBV5","http://www.ti.com/lit/ds/symlink/lmv324.pdf"
"U9,U10,U11","3","TL331","","","","Package_TO_SOT_SMD:SOT-23-5","http://www.ti.com/lit/ds/symlink/tl331.pdf"
"U12","1","AP2112K-2.6","","","","Package_TO_SOT_SMD:SOT-23-5","https://www.diodes.com/assets/Datasheets/AP2112.pdf"
"U13","1","74LVC1G332","","","","footprint:MURA160T3G","http://www.ti.com/lit/sg/scyt129e/scyt129e.pdf"

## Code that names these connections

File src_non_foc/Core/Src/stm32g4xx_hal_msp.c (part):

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    __HAL_RCC_GPIOA_CLK_ENABLE();
    __HAL_RCC_GPIOB_CLK_ENABLE();
    /**SPI1 GPIO Configuration
    PA5     ------> SPI1_SCK
    PB4     ------> SPI1_MISO
    PB5     ------> SPI1_MOSI
    */
    GPIO_InitStruct.Pin = GPIO_PIN_5;
    GPIO_InitStruct.Mode = GPIO_MODE_AF_PP;
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    __HAL_RCC_SPI1_CLK_DISABLE();

    /**SPI1 GPIO Configuration
    PA5     ------> SPI1_SCK
    PB4     ------> SPI1_MISO
    PB5     ------> SPI1_MOSI
    */
    HAL_GPIO_DeInit(GPIOA, GPIO_PIN_5);

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    __HAL_RCC_GPIOA_CLK_ENABLE();
    __HAL_RCC_GPIOB_CLK_ENABLE();
    /**TIM1 GPIO Configuration
    PF0-OSC_IN     ------> TIM1_CH3N
    PA7     ------> TIM1_CH1N
    PB0     ------> TIM1_CH2N
    PA8     ------> TIM1_CH1
    PA9     ------> TIM1_CH2
    PA10     ------> TIM1_CH3
    */
    GPIO_InitStruct.Pin = GPIO_PIN_0;
    GPIO_InitStruct.Mode = GPIO_MODE_AF_PP;
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    __HAL_RCC_TIM1_CLK_DISABLE();

    /**TIM1 GPIO Configuration
    PF0-OSC_IN     ------> TIM1_CH3N
    PA6     ------> TIM1_BKIN
    PA7     ------> TIM1_CH1N
    PB0     ------> TIM1_CH2N
    PA8     ------> TIM1_CH1
    PA9     ------> TIM1_CH2
    PA10     ------> TIM1_CH3
    */
    HAL_GPIO_DeInit(GPIOF, GPIO_PIN_0);

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
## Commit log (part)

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2026-04-26 first commit, folder structure created
2026-04-26 folder structure modified
2026-04-26 folder structure was not saved by git, so added dummy files to preserve them
2026-04-27 setup inverter electrical circuit
2026-04-27 created parameters.m file
2026-04-28 added FOC control architecture in library
2026-04-29 created schematic file and added stm32 nucleo library
2026-04-30 simulink architecture updated
2026-05-02 added some hardware to git
2026-05-03 mapped IO to stm32, generated code from stm32cubemx
2026-05-04 added decoupling in the mathematical model
2026-05-06 controller redesign in simulink
2026-05-13 changes to parameters and main slx file
2026-05-22 added hardware
2026-05-25 housekeeping files
2026-05-28 PWM shoot through current protection model added
2026-06-01 updated alternate design
2026-06-02 updates to kicad schema
2026-06-03 added OCP
2026-06-18 major additions to schematic of inverter
2026-06-24 completed project schema
2026-06-25 updated spice alternate version
2026-06-25 added status LED's to schema, fixed gate drive error, added BOM
2026-06-25 verification of gate driver circuit with proper files
2026-06-27 footprints updated in hardware
2026-06-29 hardware layout started

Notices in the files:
src_non_foc/Core/Src/stm32g4xx_hal_msp.c:
Copyright (c) 2026 STMicroelectronics.
All rights reserved.
This software is licensed under terms that can be found in the LICENSE file
